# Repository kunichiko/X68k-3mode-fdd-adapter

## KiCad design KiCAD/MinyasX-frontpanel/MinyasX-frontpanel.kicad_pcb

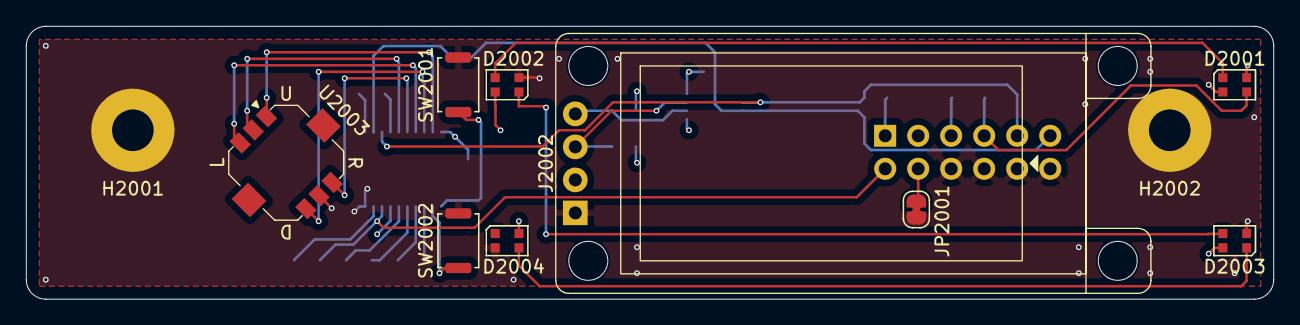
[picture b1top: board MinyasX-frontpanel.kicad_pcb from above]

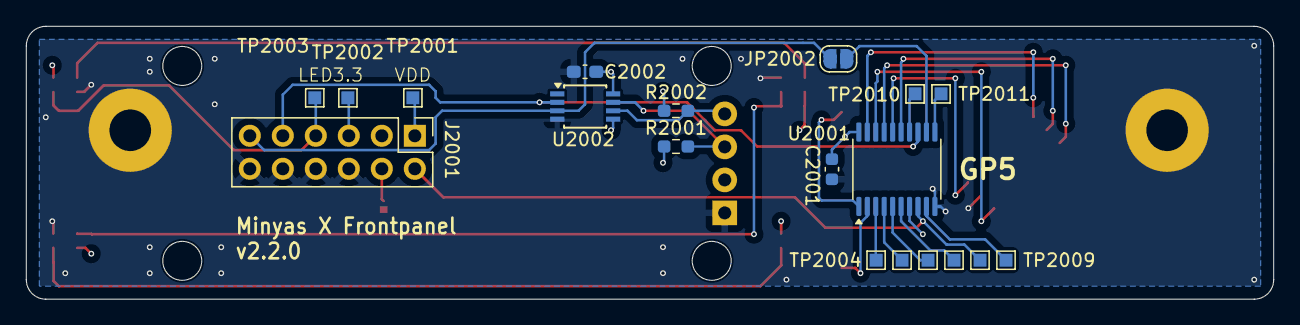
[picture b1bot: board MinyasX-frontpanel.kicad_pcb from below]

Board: 4 copper layers, 96.0 x 21.0 mm, 30 parts (19 on the bottom side), 28 nets.

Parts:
C2001: 0.1uF; C_0603_1608Metric
C2002: 0.1uF; C_0603_1608Metric_Pad1.08x0.95mm_HandSolder
D2001, D2002, D2003, D2004: WS2812B-2020; LED_WS2812B-2020_PLCC4_2.0x2.0mm
H2001, H2002: MountingHole_Pad; MountingHole_3.2mm_M3_Pad
J2001: Conn_02x06_Odd_Even; PinHeader_2x06_P2.54mm_Vertical
J2002: Conn_01x04; OLED_Dispaly_1.29inch_I2C_4pin
JP2001: Jumper_2_Bridged; SolderJumper-2_P1.3mm_Bridged_RoundedPad1.0x1.5mm
JP2002: Jumper_2_Small_Open; SolderJumper-2_P1.3mm_Open_RoundedPad1.0x1.5mm
R2001, R2002: 2.2k; R_0603_1608Metric_Pad0.98x0.95mm_HandSolder
SW2001, SW2002: SW_Push; SW_Push_SPST_NO_Alps_SKRK
TP2001, TP2002, TP2003, TP2004, TP2005, TP2006, TP2007, TP2008, TP2009, TP2010, TP2011: TestPoint; TestPoint_Pad_1.0x1.0mm
U2001: SLG46826G(V2); TSSOP-20_4.4x6.5mm_P0.65mm
U2002: PCA9515DP; TSSOP-8_3x3mm_P0.65mm
U2003: JOYSTICK; SKRHAAE010

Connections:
+3.3V: C2001.1, C2002.1, J2001.5, J2002.2, R2001.1, R2002.1, TP2002.1, U2001.7 (V_{DD2}), U2001.20 (V_{DD}), U2002.5 (EN), U2002.8 (VCC)
/CENTER: U2001.15 (IO4), U2003.2 (Center)
/CONT_PUSH: J2001.2, TP2008.1, U2001.8 (IO8)
/DOWN: U2001.18 (IO1), U2003.6 (Down)
/EJECT_A: SW2001.1, U2001.1 (IO14)
/EJECT_B: SW2002.1, U2001.2 (IO13)
/I2C_SCL: J2002.3, R2001.2, U2002.7 (SCL1)
/I2C_SCL_5V: J2001.9, U2001.13 (SCL), U2002.2 (SCL0)
/I2C_SDA: J2002.4, R2002.2, U2002.6 (SDA1)
/I2C_SDA_5V: J2001.11, JP2002.2 (B), U2002.3 (SDA0)
/LED_DATA: D2001.3 (DIN), J2001.7, TP2003.1
/LEFT: U2001.17 (IO2), U2003.3 (Left)
/RIGHT: U2001.16 (IO3), U2003.4 (Right)
/UP: U2001.19 (IO0), U2003.1 (Up)
GND: C2001.2, C2002.2, D2001.2 (VSS), D2002.2 (VSS), D2003.2 (VSS), D2004.2 (VSS), H2001.1, H2002.1, J2001.6, J2001.8, J2001.10, J2001.12, J2002.1, JP2001.2 (B), SW2001.2, SW2002.2, U2001.10 (GND), U2002.4 (GND), U2003.5 (Com)
unnamed: D2001.1 (DOUT), D2002.3 (DIN)
unnamed: D2002.1 (DOUT), D2003.3 (DIN)
unnamed: D2003.1 (DOUT), D2004.3 (DIN)
unnamed: J2001.4, JP2001.1 (A)
unnamed: JP2002.1 (A), U2001.12 (SDA)
unnamed: TP2010.1, U2001.14 (IO5)
unnamed: TP2011.1, U2001.11 (IO6)
unnamed: TP2009.1, U2001.9 (IO7)
unnamed: TP2007.1, U2001.6 (IO9)
unnamed: TP2006.1, U2001.5 (IO10)
unnamed: TP2005.1, U2001.4 (IO11)
unnamed: TP2004.1, U2001.3 (IO12)
VDD_MCU: D2001.4 (VDD), D2002.4 (VDD), D2003.4 (VDD), D2004.4 (VDD), J2001.1, TP2001.1

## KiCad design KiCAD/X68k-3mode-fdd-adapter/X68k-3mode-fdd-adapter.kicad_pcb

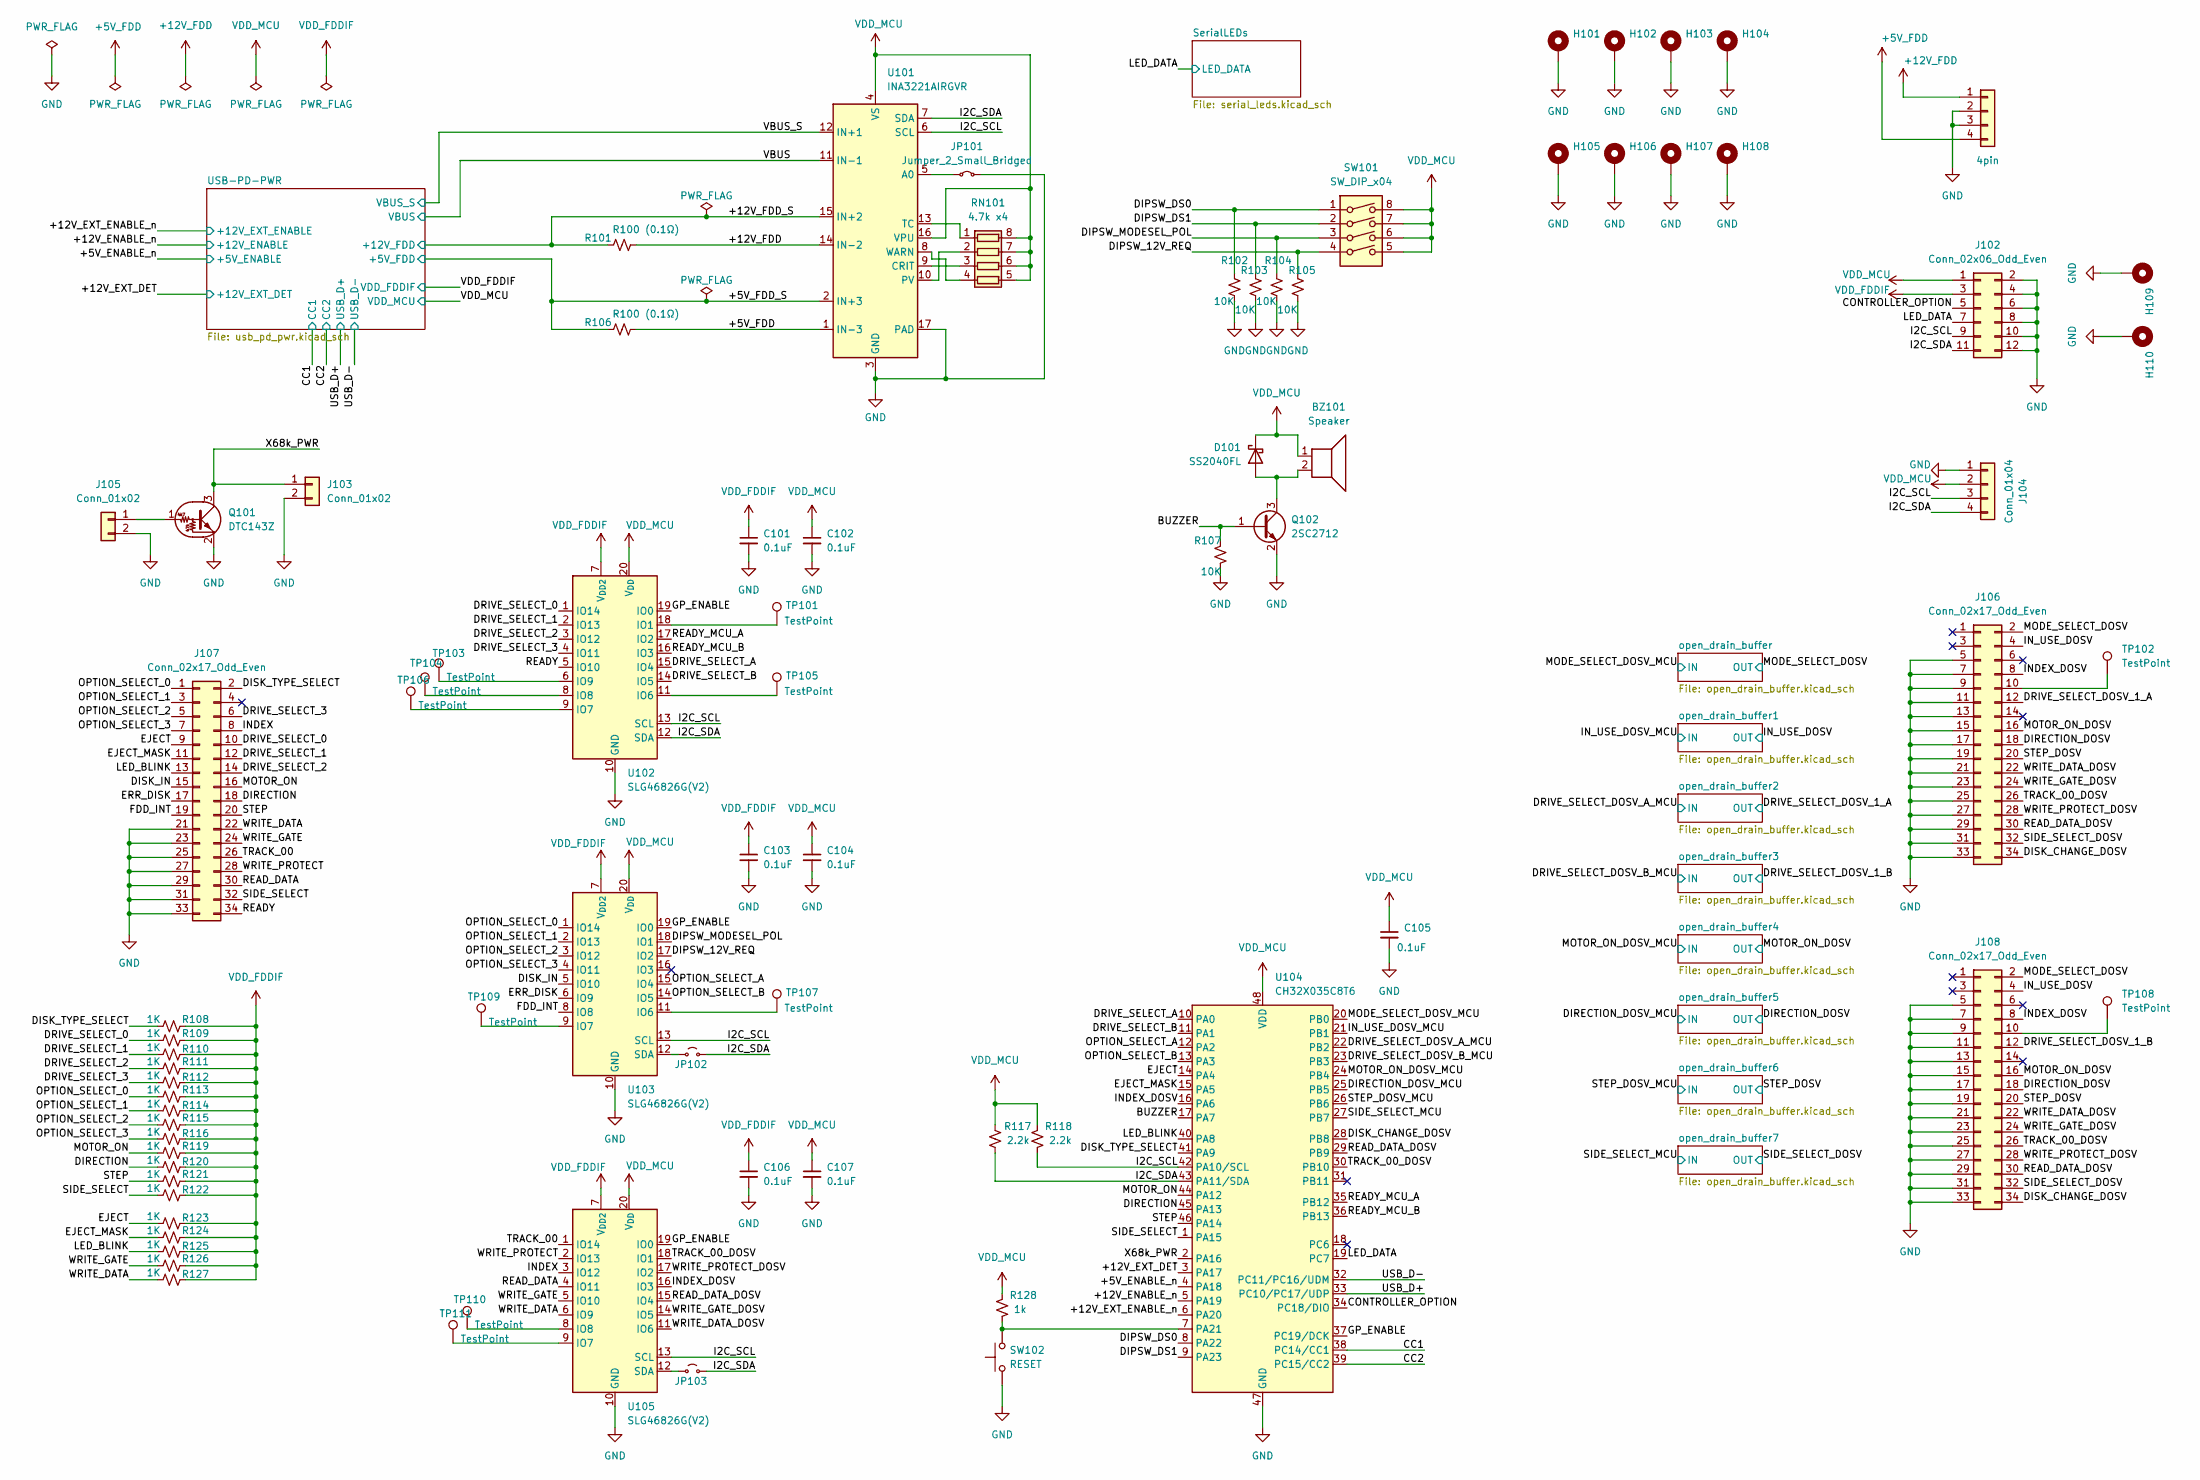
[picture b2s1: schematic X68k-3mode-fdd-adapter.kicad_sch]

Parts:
BZ101: Speaker; UGCT7525AN4
C101, C102, C103, C104, C105, C106, C107: 0.1uF; C_0603_1608Metric
D101: SS2040FL; D_SOD-123F; LCSC C268712
H101, H102, H103, H104: MountingHole_Pad; PCB_WeldingTerminal_M3_L-angle; LCSC C962334
H105, H106, H107, H108: MountingHole_Pad; MountingHole_3.2mm_M3_Pad_Small; LCSC C962334
H109: MountingHole_Pad; PCB_WeldingTerminal_M3_L-angle_PCB-54L; LCSC C962334
H110: MountingHole_Pad; PCB_WeldingTerminal_M3_L-angle_PCB-54R; LCSC C962334
J101: 4pin; TerminalBlock_Phoenix_MPT-0,5-4-2.54_1x04_P2.54mm_Horizontal; LCSC C2927505
J102: Conn_02x06_Odd_Even; PinSocket_2x06_P2.54mm_Horizontal
J103: Conn_01x02; PinHeader_1x02_P2.54mm_Vertical
J104: Conn_01x04; PinSocket_1x04_P2.54mm_Vertical
J105: Conn_01x02; JST_XH_S2B-XH-A_1x02_P2.50mm_Horizontal
J106, J108: Conn_02x17_Odd_Even; PinHeader_2x17_P2.54mm_Horizontal
J107: Conn_02x17_Odd_Even; PinHeader_2x17_P2.54mm_Horizontal_Mirror; LCSC C725929
JP101: Jumper_2_Small_Bridged; SolderJumper-2_P1.3mm_Bridged_RoundedPad1.0x1.5mm
JP102, JP103: Jumper_2_Small_Open; SolderJumper-2_P1.3mm_Open_RoundedPad1.0x1.5mm
Q101: DTC143Z; SOT-523; LCSC C5273798
Q102: 2SC2712; SOT-323_SC-70
R101, R106: R100 (0.1Ω); R_2512_6332Metric_Pad1.40x3.35mm_HandSolder
R102, R103, R104, R105, R107: 10K; R_0603_1608Metric
R108, R109, R110, R111, R112, R113, R114, R115, R116, R119, R120, R121, R122, R123, R124, R125, R126, R127: 1K; R_0603_1608Metric
R117, R118: 2.2k; R_0603_1608Metric
R128: 1k; R_0603_1608Metric
RN101: 4.7k x4; R_Array_Concave_4x0603; LCSC C1980
SW101: SW_DIP_x04; SW_DIP_SPSTx04_Slide_Copal_CHS-04B_W7.62mm_P1.27mm; LCSC C319050
SW102: RESET; SW_Push_SPST_NO_Alps_SKRK
TP101, TP102, TP103, TP104, TP105, TP106, TP107, TP108, TP109, TP110, TP111: TestPoint; TestPoint_Pad_1.0x1.0mm
U101: INA3221AIRGVR; QFN-16-1EP_4x4mm_P0.65mm_EP2.1x2.1mm_ThermalVias; LCSC C181255
U102, U103, U105: SLG46826G(V2); TSSOP-20_4.4x6.5mm_P0.65mm
U104: CH32X035C8T6; LQFP-48_7x7mm_P0.5mm

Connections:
+5V_FDD: J101.4, R106.2, U101.1 (IN-3)
+12V_FDD: J101.1, R101.2, U101.14 (IN-2)
/+5V_ENABLE_n: U104.4 (PA18); also elsewhere on the board
/+5V_FDD_S: R106.1, U101.2 (IN+3); also elsewhere on the board
/+12V_ENABLE_n: U104.5 (PA19); also elsewhere on the board
/+12V_EXT_DET: U104.3 (PA17); also elsewhere on the board
/+12V_EXT_ENABLE_n: U104.6 (PA20); also elsewhere on the board
/+12V_FDD_S: R101.1, U101.15 (IN+2); also elsewhere on the board
/BUZZER: Q102.1 (B), R107.1, U104.17 (PA7)
/CC1: U104.38 (PC14/CC1); also elsewhere on the board
/CC2: U104.39 (PC15/CC2); also elsewhere on the board
/CONTROLLER_OPTION: J102.5, U104.34 (PC18/DIO)
/DIPSW_12V_REQ: R105.1, SW101.4, U103.17 (IO2)
/DIPSW_DS0: R102.1, SW101.1, U104.8 (PA22)
/DIPSW_DS1: R103.1, SW101.2, U104.9 (PA23)
/DIPSW_MODESEL_POL: R104.1, SW101.3, U103.18 (IO1)
/DIRECTION: J107.18, R120.2, U104.45 (PA13)
/DIRECTION_DOSV: J106.18, J108.18; also elsewhere on the board
/DIRECTION_DOSV_MCU: U104.25 (PB5); also elsewhere on the board
/DISK_CHANGE_DOSV: J106.34, J108.34, U104.28 (PB8)
/DISK_IN: J107.15, U103.5 (IO10)
/DISK_TYPE_SELECT: J107.2, R108.2, U104.41 (PA9)
/DRIVE_SELECT_0: J107.10, R109.2, U102.1 (IO14)
/DRIVE_SELECT_1: J107.12, R110.2, U102.2 (IO13)
/DRIVE_SELECT_2: J107.14, R111.2, U102.3 (IO12)
/DRIVE_SELECT_3: J107.6, R112.2, U102.4 (IO11)
/DRIVE_SELECT_A: U102.15 (IO4), U104.10 (PA0)
/DRIVE_SELECT_B: U102.14 (IO5), U104.11 (PA1)
/DRIVE_SELECT_DOSV_1_A: J106.12; also elsewhere on the board
/DRIVE_SELECT_DOSV_1_B: J108.12; also elsewhere on the board
/DRIVE_SELECT_DOSV_A_MCU: U104.22 (PB2); also elsewhere on the board
/DRIVE_SELECT_DOSV_B_MCU: U104.23 (PB3); also elsewhere on the board
/EJECT: J107.9, R123.2, U104.14 (PA4)
/EJECT_MASK: J107.11, R124.2, U104.15 (PA5)
/ERR_DISK: J107.17, U103.6 (IO9)
/FDD_INT: J107.19, U103.8 (IO8)
/GP_ENABLE: U102.19 (IO0), U103.19 (IO0), U104.37 (PC19/DCK), U105.19 (IO0)
/I2C_SCL: J102.9, J104.3, R118.2, U101.6 (SCL), U102.13 (SCL), U103.13 (SCL), U104.42 (PA10/SCL), U105.13 (SCL)
/I2C_SDA: J102.11, J104.4, JP102.2 (B), JP103.2 (B), R117.2, U101.7 (SDA), U102.12 (SDA), U104.43 (PA11/SDA)
/INDEX: J107.8, U105.3 (IO12)
/INDEX_DOSV: J106.8, J108.8, U104.16 (PA6), U105.16 (IO3)
/IN_USE_DOSV: J106.4, J108.4; also elsewhere on the board
/IN_USE_DOSV_MCU: U104.21 (PB1); also elsewhere on the board
/LED_BLINK: J107.13, R125.2, U104.40 (PA8)
/LED_DATA: J102.7, U104.19 (PC7); also elsewhere on the board
/MODE_SELECT_DOSV: J106.2, J108.2; also elsewhere on the board
/MODE_SELECT_DOSV_MCU: U104.20 (PB0); also elsewhere on the board
/MOTOR_ON: J107.16, R119.2, U104.44 (PA12)
/MOTOR_ON_DOSV: J106.16, J108.16; also elsewhere on the board
/MOTOR_ON_DOSV_MCU: U104.24 (PB4); also elsewhere on the board
/OPTION_SELECT_0: J107.1, R113.2, U103.1 (IO14)
/OPTION_SELECT_1: J107.3, R114.2, U103.2 (IO13)
/OPTION_SELECT_2: J107.5, R115.2, U103.3 (IO12)
/OPTION_SELECT_3: J107.7, R116.2, U103.4 (IO11)
/OPTION_SELECT_A: U103.15 (IO4), U104.12 (PA2)
/OPTION_SELECT_B: U103.14 (IO5), U104.13 (PA3)
/READY: J107.34, U102.5 (IO10)
/READY_MCU_A: U102.17 (IO2), U104.35 (PB12)
/READY_MCU_B: U102.16 (IO3), U104.36 (PB13)
/READ_DATA: J107.30, U105.4 (IO11)
/READ_DATA_DOSV: J106.30, J108.30, U104.29 (PB9), U105.15 (IO4)
/SIDE_SELECT: J107.32, R122.2, U104.1 (PA15)
/SIDE_SELECT_DOSV: J106.32, J108.32; also elsewhere on the board
/SIDE_SELECT_MCU: U104.27 (PB7); also elsewhere on the board
/STEP: J107.20, R121.2, U104.46 (PA14)
/STEP_DOSV: J106.20, J108.20; also elsewhere on the board
/STEP_DOSV_MCU: U104.26 (PB6); also elsewhere on the board
/TRACK_00: J107.26, U105.1 (IO14)
/TRACK_00_DOSV: J106.26, J108.26, U104.30 (PB10), U105.18 (IO1)
/USB_D+: U104.33 (PC10/PC17/UDP); also elsewhere on the board
/USB_D-: U104.32 (PC11/PC16/UDM); also elsewhere on the board
/VBUS: U101.11 (IN-1); also elsewhere on the board
/VBUS_S: U101.12 (IN+1); also elsewhere on the board
/WRITE_DATA: J107.22, R127.2, U105.6 (IO9)
/WRITE_DATA_DOSV: J106.22, J108.22, U105.11 (IO6)
/WRITE_GATE: J107.24, R126.2, U105.5 (IO10)
/WRITE_GATE_DOSV: J106.24, J108.24, U105.14 (IO5)
/WRITE_PROTECT: J107.28, U105.2 (IO13)
/WRITE_PROTECT_DOSV: J106.28, J108.28, U105.17 (IO2)
/X68k_PWR: J103.1, Q101.3 (C), U104.2 (PA16)
GND: C101.2, C102.2, C103.2, C104.2, C105.2, C106.2, C107.2, H101.1, H102.1, H103.1, H104.1, H105.1, H106.1, H107.1, H108.1, H109.1, H110.1, J101.2, J101.3, J102.2, J102.4, J102.6, J102.8, J102.10, J102.12, J103.2, J104.1, J105.2, J106.5, J106.7, J106.9, J106.11, J106.13, J106.15, J106.17, J106.19, J106.21, J106.23, J106.25, J106.27, J106.29, J106.31, J106.33, J107.21, J107.23, J107.25, J107.27, J107.29, J107.31, J107.33, J108.5, J108.7, J108.9, J108.11, J108.13, J108.15, J108.17, J108.19, J108.21, J108.23, J108.25, J108.27, J108.29, J108.31, J108.33, JP101.2 (B), Q101.2 (E), Q102.2 (E), R102.2, R103.2, R104.2, R105.2, R107.2, SW102.1, U101.3 (GND), U101.17 (PAD), U102.10 (GND), U103.10 (GND), U104.47 (GND), U105.10 (GND); also elsewhere on the board
unnamed: BZ101.2, D101.2 (A), Q102.3 (C)
unnamed: J105.1, Q101.1 (B)
unnamed: J106.10, TP102.1
unnamed: J108.10, TP108.1
unnamed: JP101.1 (A), U101.5 (A0)
unnamed: JP102.1 (A), U103.12 (SDA)
unnamed: JP103.1 (A), U105.12 (SDA)
unnamed: RN101.1 (R1.1), U101.13 (TC)
unnamed: RN101.2 (R2.1), U101.10 (PV)
unnamed: RN101.3 (R3.1), U101.9 (CRIT)
unnamed: RN101.4 (R4.1), U101.8 (WARN)
unnamed: TP101.1, U102.18 (IO1)
unnamed: TP105.1, U102.11 (IO6)
unnamed: TP106.1, U102.9 (IO7)
unnamed: TP104.1, U102.8 (IO8)
unnamed: TP103.1, U102.6 (IO9)
unnamed: TP107.1, U103.11 (IO6)
unnamed: TP109.1, U103.9 (IO7)
unnamed: R128.2, SW102.2, U104.7 (PA21)
unnamed: TP111.1, U105.9 (IO7)
unnamed: TP110.1, U105.8 (IO8)
VDD_FDDIF: C101.1, C103.1, C106.1, J102.3, R108.1, R109.1, R110.1, R111.1, R112.1, R113.1, R114.1, R115.1, R116.1, R119.1, R120.1, R121.1, R122.1, R123.1, R124.1, R125.1, R126.1, R127.1, U102.7 (V_{DD2}), U103.7 (V_{DD2}), U105.7 (V_{DD2}); also elsewhere on the board
VDD_MCU: BZ101.1, C102.1, C104.1, C105.1, C107.1, D101.1 (K), J102.1, J104.2, R117.1, R118.1, R128.1, RN101.5 (R4.2), RN101.6 (R3.2), RN101.7 (R2.2), RN101.8 (R1.2), SW101.5, SW101.6, SW101.7, SW101.8, U101.4 (VS), U101.16 (VPU), U102.20 (V_{DD}), U103.20 (V_{DD}), U104.48 (VDD), U105.20 (V_{DD}); also elsewhere on the board

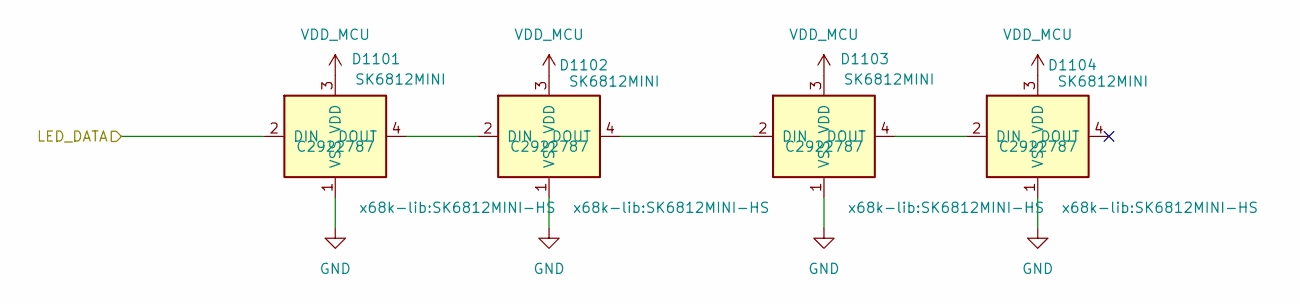
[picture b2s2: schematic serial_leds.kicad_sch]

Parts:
D1101, D1102, D1103, D1104: SK6812MINI; SK6812MINI-HS; LCSC C2922787

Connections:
/LED_DATA: D1101.2 (DIN); also elsewhere on the board
GND: D1101.1 (VSS), D1102.1 (VSS), D1103.1 (VSS), D1104.1 (VSS); also elsewhere on the board
unnamed: D1101.4 (DOUT), D1102.2 (DIN)
unnamed: D1102.4 (DOUT), D1103.2 (DIN)
unnamed: D1103.4 (DOUT), D1104.2 (DIN)
VDD_MCU: D1101.3 (VDD), D1102.3 (VDD), D1103.3 (VDD), D1104.3 (VDD); also elsewhere on the board

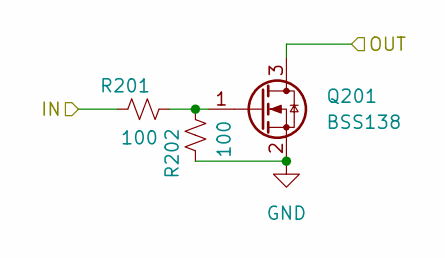
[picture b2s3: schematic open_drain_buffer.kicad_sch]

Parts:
Q201: BSS138; SOT-23
R201, R202: 100; R_0603_1608Metric

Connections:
/MODE_SELECT_DOSV: Q201.3 (D); also elsewhere on the board
/MODE_SELECT_DOSV_MCU: R201.1; also elsewhere on the board
GND: Q201.2 (S), R202.1; also elsewhere on the board
unnamed: Q201.1 (G), R201.2, R202.2

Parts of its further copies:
Q301, Q401, Q501, Q601, Q701, Q801, Q901: BSS138; SOT-23
R301, R302, R401, R402, R501, R502, R601, R602, R701, R702, R801, R802, R901, R902: 100; R_0603_1608Metric

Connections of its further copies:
/DIRECTION_DOSV: Q701.3 (D); also elsewhere on the board
/DIRECTION_DOSV_MCU: R701.1; also elsewhere on the board
/DRIVE_SELECT_DOSV_1_A: Q401.3 (D); also elsewhere on the board
/DRIVE_SELECT_DOSV_1_B: Q501.3 (D); also elsewhere on the board
/DRIVE_SELECT_DOSV_A_MCU: R401.1; also elsewhere on the board
/DRIVE_SELECT_DOSV_B_MCU: R501.1; also elsewhere on the board
/IN_USE_DOSV: Q301.3 (D); also elsewhere on the board
/IN_USE_DOSV_MCU: R301.1; also elsewhere on the board
/MOTOR_ON_DOSV: Q601.3 (D); also elsewhere on the board
/MOTOR_ON_DOSV_MCU: R601.1; also elsewhere on the board
/SIDE_SELECT_DOSV: Q901.3 (D); also elsewhere on the board
/SIDE_SELECT_MCU: R901.1; also elsewhere on the board
/STEP_DOSV: Q801.3 (D); also elsewhere on the board
/STEP_DOSV_MCU: R801.1; also elsewhere on the board
GND: Q301.2 (S), Q401.2 (S), Q501.2 (S), Q601.2 (S), Q701.2 (S), Q801.2 (S), Q901.2 (S), R302.1, R402.1, R502.1, R602.1, R702.1, R802.1, R902.1; also elsewhere on the board
unnamed: Q301.1 (G), R301.2, R302.2
unnamed: Q401.1 (G), R401.2, R402.2
unnamed: Q501.1 (G), R501.2, R502.2
unnamed: Q601.1 (G), R601.2, R602.2
unnamed: Q701.1 (G), R701.2, R702.2
unnamed: Q801.1 (G), R801.2, R802.2
unnamed: Q901.1 (G), R901.2, R902.2

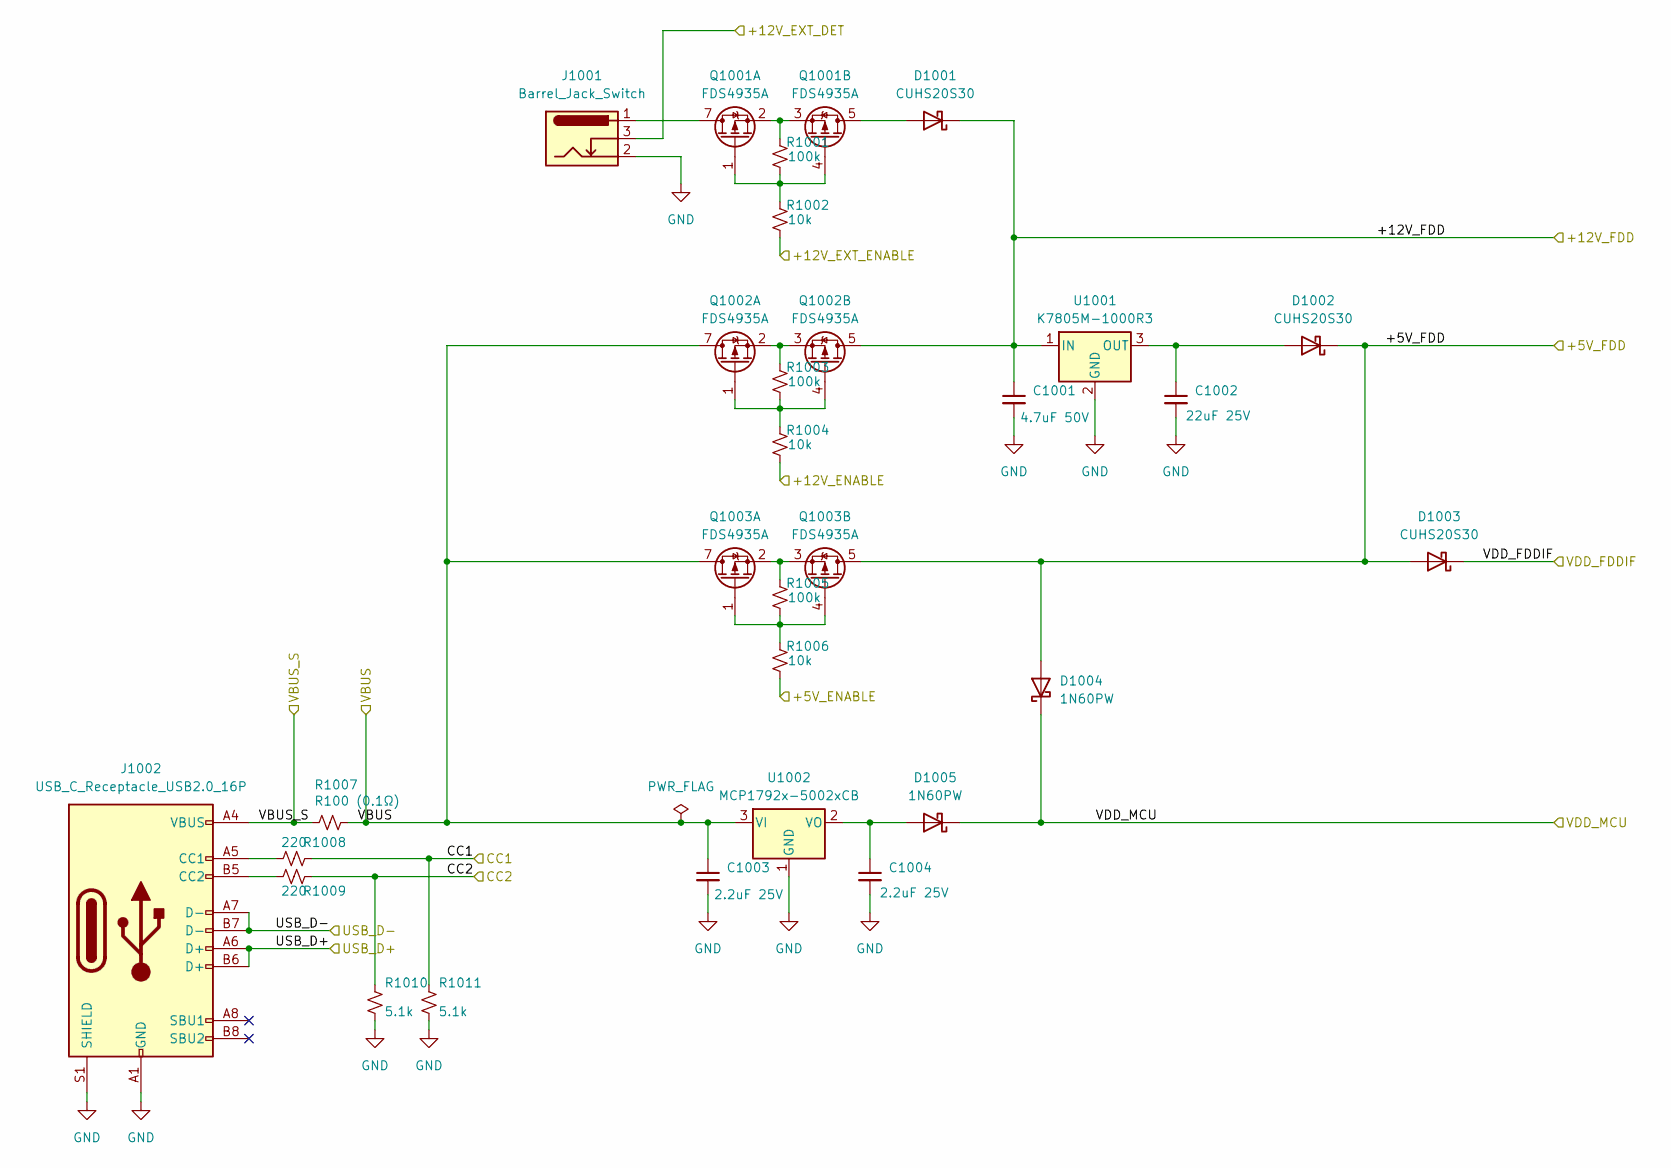
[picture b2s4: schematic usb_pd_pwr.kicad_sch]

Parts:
C1001: 4.7uF 50V; C_1206_3216Metric_Pad1.33x1.80mm_HandSolder; LCSC C51205
C1002: 22uF 25V; C_0805_2012Metric_Pad1.18x1.45mm_HandSolder; LCSC C602037
C1003: 2.2uF 25V; C_0805_2012Metric_Pad1.18x1.45mm_HandSolder; LCSC C19110
C1004: 2.2uF 25V; C_0805_2012Metric_Pad1.18x1.45mm_HandSolder
D1001, D1002, D1003: CUHS20S30; CUHS20S30 (US2H); LCSC C5636538
D1004, D1005: 1N60PW; D_SOD-123; LCSC C134188
J1001: Barrel_Jack_Switch; BarrelJack_Horizontal
J1002: USB_C_Receptacle_USB2.0_16P; USB_C_Receptacle_G-Switch_GT-USB-7010ASV; LCSC C2765186
Q1001, Q1002, Q1003: FDS4935A; SOIC-8_3.9x4.9mm_P1.27mm
R1001, R1003, R1005: 100k; R_0603_1608Metric
R1002, R1004, R1006: 10k; R_0603_1608Metric
R1007: R100 (0.1Ω); R_2512_6332Metric_Pad1.40x3.35mm_HandSolder
R1008, R1009: 220; R_0603_1608Metric
R1010, R1011: 5.1k; R_0603_1608Metric
U1001: K7805M-1000R3; Converter_DCDC_RECOM_R-78E-0.5_THT; LCSC C5369649
U1002: MCP1792x-5002xCB; SOT-23

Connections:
/+5V_ENABLE_n: R1006.2; also elsewhere on the board
/+5V_FDD_S: D1002.1 (K), D1003.2 (A), D1004.2 (A), Q1003.5 (D2), Q1003.6 (D2); also elsewhere on the board
/+12V_ENABLE_n: R1004.2; also elsewhere on the board
/+12V_EXT_DET: J1001.3; also elsewhere on the board
/+12V_EXT_ENABLE_n: R1002.2; also elsewhere on the board
/+12V_FDD_S: C1001.1, D1001.1 (K), Q1002.5 (D2), Q1002.6 (D2), U1001.1 (IN); also elsewhere on the board
/CC1: R1008.2, R1011.1; also elsewhere on the board
/CC2: R1009.2, R1010.1; also elsewhere on the board
/USB_D+: J1002.A6 (D+), J1002.B6 (D+); also elsewhere on the board
/USB_D-: J1002.A7 (D-), J1002.B7 (D-); also elsewhere on the board
/VBUS: C1003.1, Q1002.7 (D2), Q1002.8 (D2), Q1003.7 (D2), Q1003.8 (D2), R1007.1, U1002.3 (VI); also elsewhere on the board
/VBUS_S: J1002.A4 (VBUS), J1002.A9 (VBUS), J1002.B4 (VBUS), J1002.B9 (VBUS), R1007.2; also elsewhere on the board
GND: C1001.2, C1002.2, C1003.2, C1004.2, J1001.2, J1002.A1 (GND), J1002.A12 (GND), J1002.B1 (GND), J1002.B12 (GND), J1002.S1 (SHIELD), R1010.2, R1011.2, U1001.2 (GND), U1002.1 (GND); also elsewhere on the board
unnamed: D1001.2 (A), Q1001.5 (D2), Q1001.6 (D2)
unnamed: C1002.1, D1002.2 (A), U1001.3 (OUT)
unnamed: C1004.1, D1005.2 (A), U1002.2 (VO)
unnamed: J1001.1, Q1001.7 (D2), Q1001.8 (D2)
unnamed: J1002.A5 (CC1), R1008.1
unnamed: J1002.B5 (CC2), R1009.1
unnamed: Q1001.1 (G2), Q1001.4 (G2), R1001.2, R1002.1
unnamed: Q1001.2 (S2), Q1001.3 (S2), R1001.1
unnamed: Q1002.1 (G2), Q1002.4 (G2), R1003.2, R1004.1
unnamed: Q1002.2 (S2), Q1002.3 (S2), R1003.1
unnamed: Q1003.1 (G2), Q1003.4 (G2), R1005.2, R1006.1
unnamed: Q1003.2 (S2), Q1003.3 (S2), R1005.1
VDD_FDDIF: D1003.1 (K); also elsewhere on the board
VDD_MCU: D1004.1 (K), D1005.1 (K); also elsewhere on the board

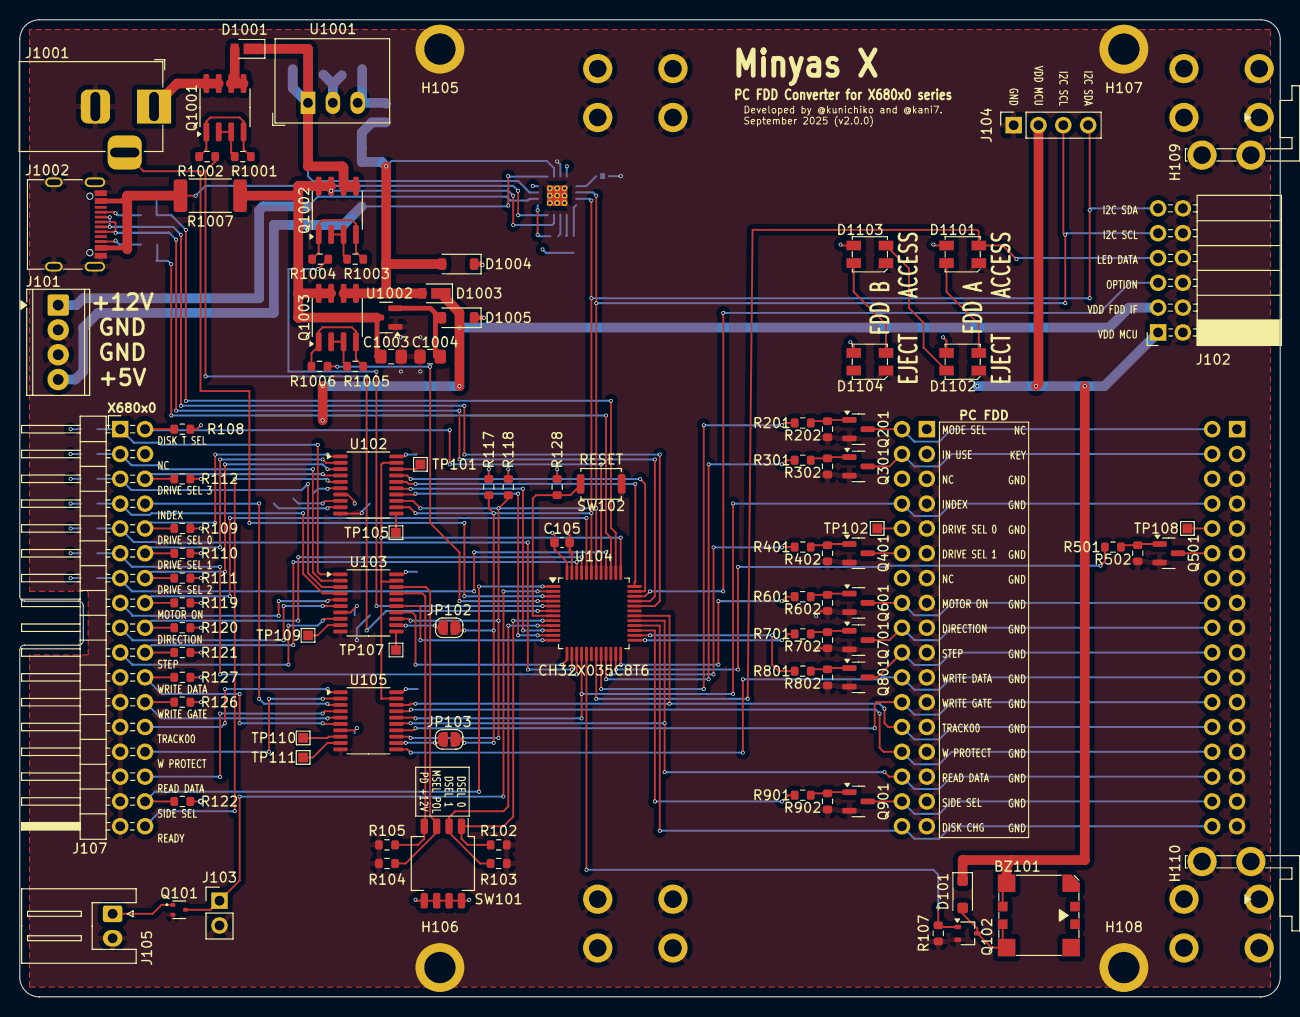
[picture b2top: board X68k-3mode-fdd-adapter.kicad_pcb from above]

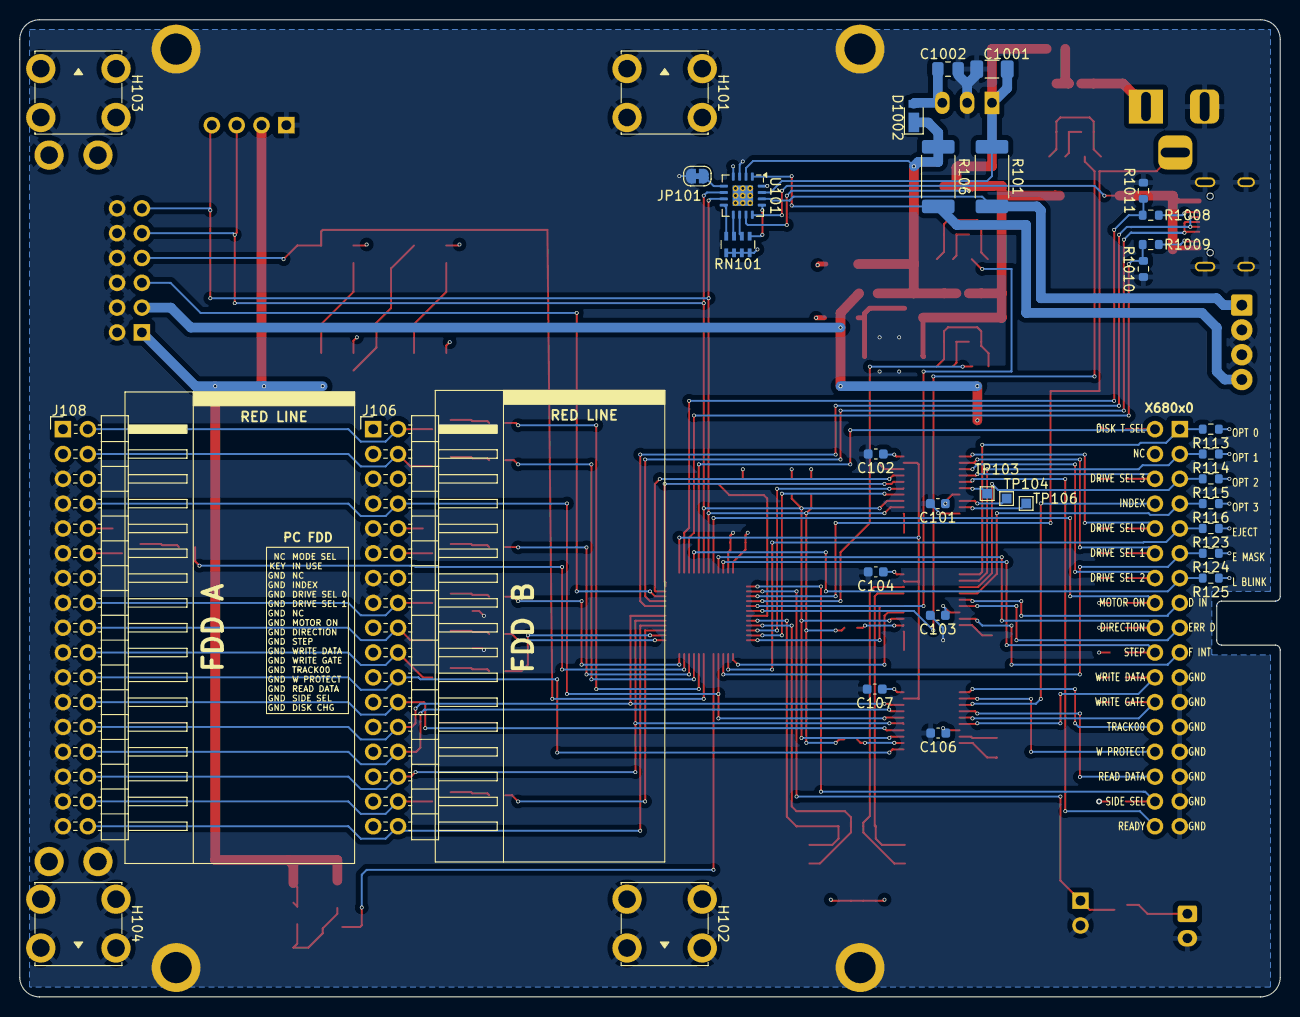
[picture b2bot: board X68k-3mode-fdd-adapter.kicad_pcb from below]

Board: 4 copper layers, 129.0 x 100.0 mm, 134 parts (34 on the bottom side), 127 nets.

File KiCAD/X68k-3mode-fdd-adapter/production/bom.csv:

Designator,Footprint,Quantity,Value,LCSC Part #
BZ101,UGCT7525AN4,1,Speaker,
C1001,1206,1,4.7uF 50V,C51205
C1002,0805,1,22uF 25V,C602037
C1003,0805,1,2.2uF 25V,C19110
C1004,0805,1,2.2uF 25V,
"C101, C102, C103, C104, C105, C106, C107",0603,7,0.1uF,
"D1001, D1002, D1003",CUHS20S30 (US2H),3,CUHS20S30,C5636538
"D1004, D1005",D_SOD-123,2,1N60PW,C134188
D101,D_SOD-123F,1,SS2040FL,C268712
"D1101, D1102, D1103, D1104",SK6812MINI-HS,4,SK6812MINI,C2922787
J1001,BarrelJack_Horizontal,1,Barrel_Jack_Switch,
J1002,USB_C_Receptacle_G-Switch_GT-USB-7010ASV,1,USB_C_Receptacle_USB2.0_16P,C2765186
J101,"TerminalBlock_Phoenix_MPT-0,5-4-2.54_1x04_P2.54mm_Horizontal",1,4pin,C2927505
J102,PinSocket_2x06_P2.54mm_Horizontal,1,Conn_02x06_Odd_Even,
J103,PinHeader_1x02_P2.54mm_Vertical,1,Conn_01x02,
J104,PinSocket_1x04_P2.54mm_Vertical,1,Conn_01x04,
J105,JST_XH_S2B-XH-A_1x02_P2.50mm_Horizontal,1,Conn_01x02,
"J106, J108",PinHeader_2x17_P2.54mm_Horizontal,2,Conn_02x17_Odd_Even,
J107,PinHeader_2x17_P2.54mm_Horizontal_Mirror,1,Conn_02x17_Odd_Even,C725929
JP101,SolderJumper-2_P1.3mm_Bridged_RoundedPad1.0x1.5mm,1,Jumper_2_Small_Bridged,
"JP102, JP103",SolderJumper-2_P1.3mm_Open_RoundedPad1.0x1.5mm,2,Jumper_2_Small_Open,
"Q1001, Q1002, Q1003",SOIC-8_3.9x4.9mm_P1.27mm,3,FDS4935A,
Q101,SOT-523,1,DTC143Z,C5273798
Q102,SOT-323_SC-70,1,2SC2712,
"Q201, Q301, Q401, Q501, Q601, Q701, Q801, Q901",SOT-23,8,BSS138,
"R1001, R1003, R1005",0603,3,100k,
"R1002, R1004, R1006, R102, R103, R104, R105, R107",0603,8,10k,
"R1007, R101, R106",2512,3,R100 (0.1Ω),
"R1008, R1009",0603,2,220,
"R1010, R1011",0603,2,5.1k,
"R108, R109, R110, R111, R112, R113, R114, R115, R116, R119, R120, R121, R122, R123, R124, R125, R126, R127, R128",0603,19,1K,
"R117, R118",0603,2,2.2k,
"R201, R202, R301, R302, R401, R402, R501, R502, R601, R602, R701, R702, R801, R802, R901, R902",0603,16,100,
RN101,R_Array_Concave_4x0603,1,4.7k x4,C1980
SW101,SW_DIP_SPSTx04_Slide_Copal_CHS-04B_W7.62mm_P1.27mm,1,SW_DIP_x04,C319050
SW102,SW_Push_SPST_NO_Alps_SKRK,1,RESET,
"TP101, TP102, TP103, TP104, TP105, TP106, TP107, TP108, TP109, TP110, TP111",TestPoint_Pad_1.0x1.0mm,11,TestPoint,
U1001,Converter_DCDC_RECOM_R-78E-0.5_THT,1,K7805M-1000R3,C5369649
U1002,SOT-23,1,MCP1792x-5002xCB,
U101,QFN-16-1EP_4x4mm_P0.65mm_EP2.1x2.1mm_ThermalVias,1,INA3221AIRGVR,C181255
"U102, U103, U105",TSSOP-20_4.4x6.5mm_P0.65mm,3,SLG46826G(V2),
U104,LQFP-48_7x7mm_P0.5mm,1,CH32X035C8T6,
